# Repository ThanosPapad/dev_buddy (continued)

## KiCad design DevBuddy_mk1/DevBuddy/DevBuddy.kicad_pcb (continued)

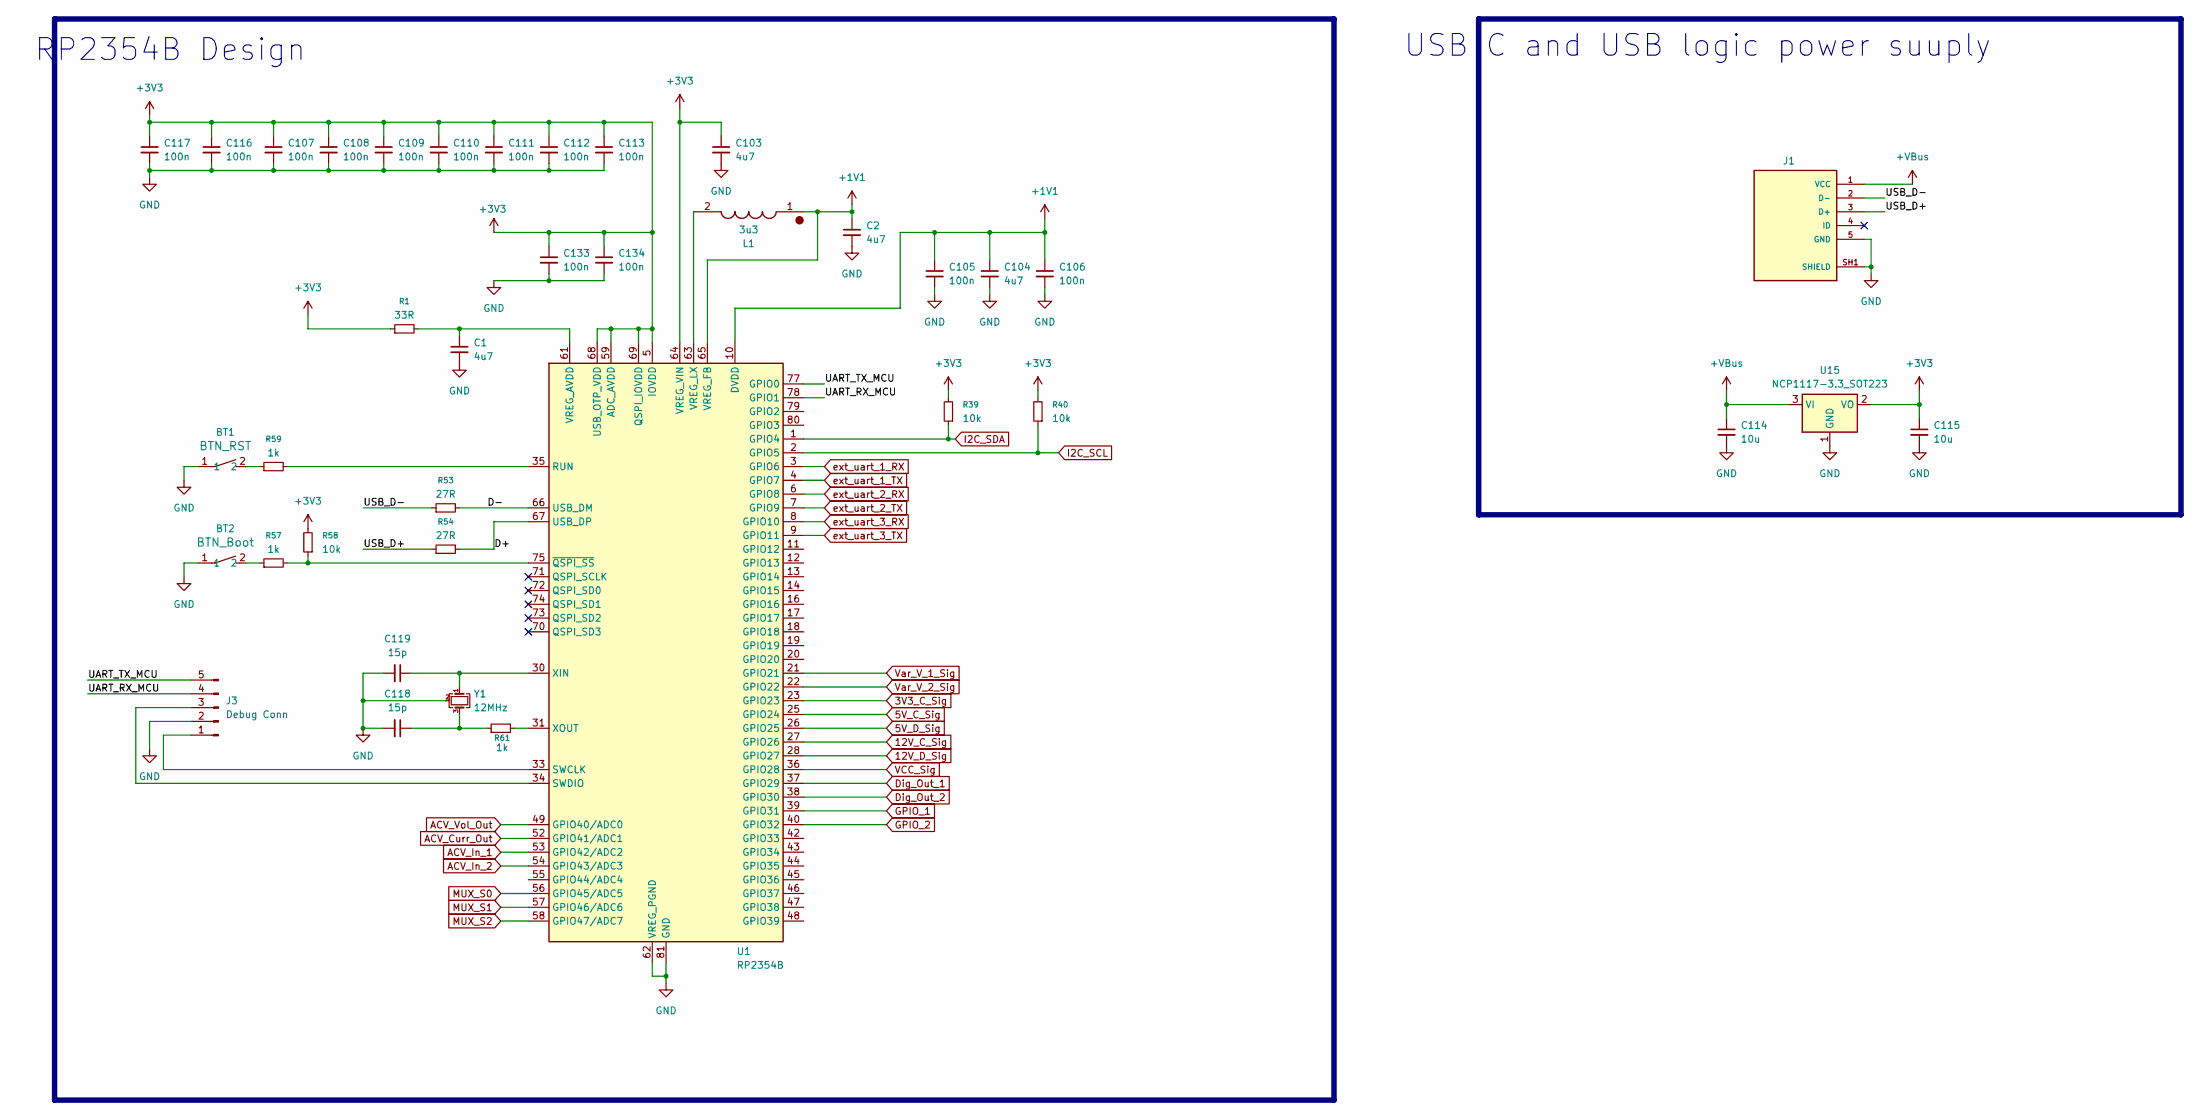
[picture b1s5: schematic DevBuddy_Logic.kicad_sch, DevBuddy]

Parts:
BT1: BTN_RST; B3U-1000P
BT2: BTN_Boot; B3U-1000P
C1, C2, C103, C104: 4u7; C_0402_1005Metric
C105, C106, C107, C108, C109, C110, C111, C112, C113, C116, C117, C133, C134: 100n; C_0402_1005Metric
C114, C115: 10u; C_0805_2012Metric
C118, C119: 15p; C_0402_1005Metric
J1: 10118194-0001LF; AMPHENOL_10118194-0001LF; PARTREV D
J3: Debug Conn; PinHeader_1x05_P2.54mm_Vertical_SMD_Pin1Left
L1: 3u3; AOTAB201610S3R3101T; Mouser Part Number 815-AB201610S3R3101T
R1: 33R; R_0402_1005Metric
R39, R40, R58: 10k; R_0402_1005Metric
R53, R54: 27R; R_0402_1005Metric
R57, R59, R61: 1k; R_0402_1005Metric
U1: RP2354B; QFN-80-1EP_10x10mm_P0.4mm_EP3.4x3.4mm
U15: NCP1117-3.3_SOT223; SOT-223-3_TabPin2
Y1: 12MHz; Crystal_SMD_3225-4Pin_3.2x2.5mm

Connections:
3V3_C_Sig: U1.23 (GPIO23); also elsewhere on the board
5V_C_Sig: U1.25 (GPIO24); also elsewhere on the board
5V_D_Sig: U1.26 (GPIO25); also elsewhere on the board
12V_C_Sig: U1.27 (GPIO26); also elsewhere on the board
12V_D_Sig: U1.28 (GPIO27); also elsewhere on the board
+1V1: C2.1, C104.1, C105.1, C106.1, L1.1, U1.10 (DVDD), U1.32 (DVDD), U1.51 (DVDD), U1.65 (VREG_FB)
+3V3: C103.1, C107.1, C108.1, C109.1, C110.1, C111.1, C112.1, C113.1, C115.1, C116.1, C117.1, C133.1, C134.1, R1.1, R39.2, R40.2, R58.2, U1.5 (IOVDD), U1.15 (IOVDD), U1.24 (IOVDD), U1.29 (IOVDD), U1.41 (IOVDD), U1.50 (IOVDD), U1.59 (ADC_AVDD), U1.60 (IOVDD), U1.64 (VREG_VIN), U1.68 (USB_OTP_VDD), U1.69 (QSPI_IOVDD), U1.76 (IOVDD), U15.2 (VO); also elsewhere on the board
+VBus: C114.1, J1.1 (VCC), U15.3 (VI)
/DevBuddy_Logic/D+: R54.2, U1.67 (USB_DP)
/DevBuddy_Logic/D-: R53.2, U1.66 (USB_DM)
/DevBuddy_Logic/UART_RX_MCU: J3.4, U1.78 (GPIO1)
/DevBuddy_Logic/UART_TX_MCU: J3.5, U1.77 (GPIO0)
/DevBuddy_Logic/USB_D+: J1.3 (D+), R54.1
/DevBuddy_Logic/USB_D-: J1.2 (D-), R53.1
ACV_Curr_Out: U1.52 (GPIO41/ADC1); also elsewhere on the board
ACV_In_1: U1.53 (GPIO42/ADC2); also elsewhere on the board
ACV_In_2: U1.54 (GPIO43/ADC3); also elsewhere on the board
ACV_Vol_Out: U1.49 (GPIO40/ADC0); also elsewhere on the board
Dig_Out_1: U1.37 (GPIO29); also elsewhere on the board
Dig_Out_2: U1.38 (GPIO30); also elsewhere on the board
GND: BT1.1, BT2.1, C1.2, C2.2, C103.2, C104.2, C105.2, C106.2, C107.2, C108.2, C109.2, C110.2, C111.2, C112.2, C113.2, C114.2, C115.2, C116.2, C117.2, C118.2, C119.2, C133.2, C134.2, J1.5 (GND), J1.SH1 (SHIELD), J1.SH2 (SHIELD), J1.SH3 (SHIELD), J1.SH4 (SHIELD), J1.SH5 (SHIELD), J1.SH6 (SHIELD), J3.2, U1.62 (VREG_PGND), U1.81 (GND), U15.1 (GND), Y1.2 (G), Y1.4 (G); also elsewhere on the board
GPIO_1: U1.39 (GPIO31); also elsewhere on the board
GPIO_2: U1.40 (GPIO32); also elsewhere on the board
I2C_SCL: R40.1, U1.2 (GPIO5); also elsewhere on the board
I2C_SDA: R39.1, U1.1 (GPIO4); also elsewhere on the board
MUX_S0: U1.56 (GPIO45/ADC5); also elsewhere on the board
MUX_S1: U1.57 (GPIO46/ADC6); also elsewhere on the board
MUX_S2: U1.58 (GPIO47/ADC7); also elsewhere on the board
unnamed: BT1.2, R59.1
unnamed: BT2.2, R57.1
unnamed: C118.1, R61.1, Y1.3
unnamed: J3.1, U1.33 (SWCLK)
unnamed: J3.3, U1.34 (SWDIO)
unnamed: R59.2, U1.35 (RUN)
unnamed: C1.1, R1.2, U1.61 (VREG_AVDD)
unnamed: L1.2, U1.63 (VREG_LX)
unnamed: C119.1, U1.30 (XIN), Y1.1
unnamed: R61.2, U1.31 (XOUT)
unnamed: R57.2, R58.1, U1.75 (~QSPI_SS)
VCC_Sig: U1.36 (GPIO28); also elsewhere on the board
Var_V_1_Sig: U1.21 (GPIO21); also elsewhere on the board
Var_V_2_Sig: U1.22 (GPIO22); also elsewhere on the board
ext_uart_1_RX: U1.3 (GPIO6); also elsewhere on the board
ext_uart_1_TX: U1.4 (GPIO7); also elsewhere on the board
ext_uart_2_RX: U1.6 (GPIO8); also elsewhere on the board
ext_uart_2_TX: U1.7 (GPIO9); also elsewhere on the board
ext_uart_3_RX: U1.8 (GPIO10); also elsewhere on the board
ext_uart_3_TX: U1.9 (GPIO11); also elsewhere on the board

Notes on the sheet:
RP2354B Design
USB C and USB logic power suuply

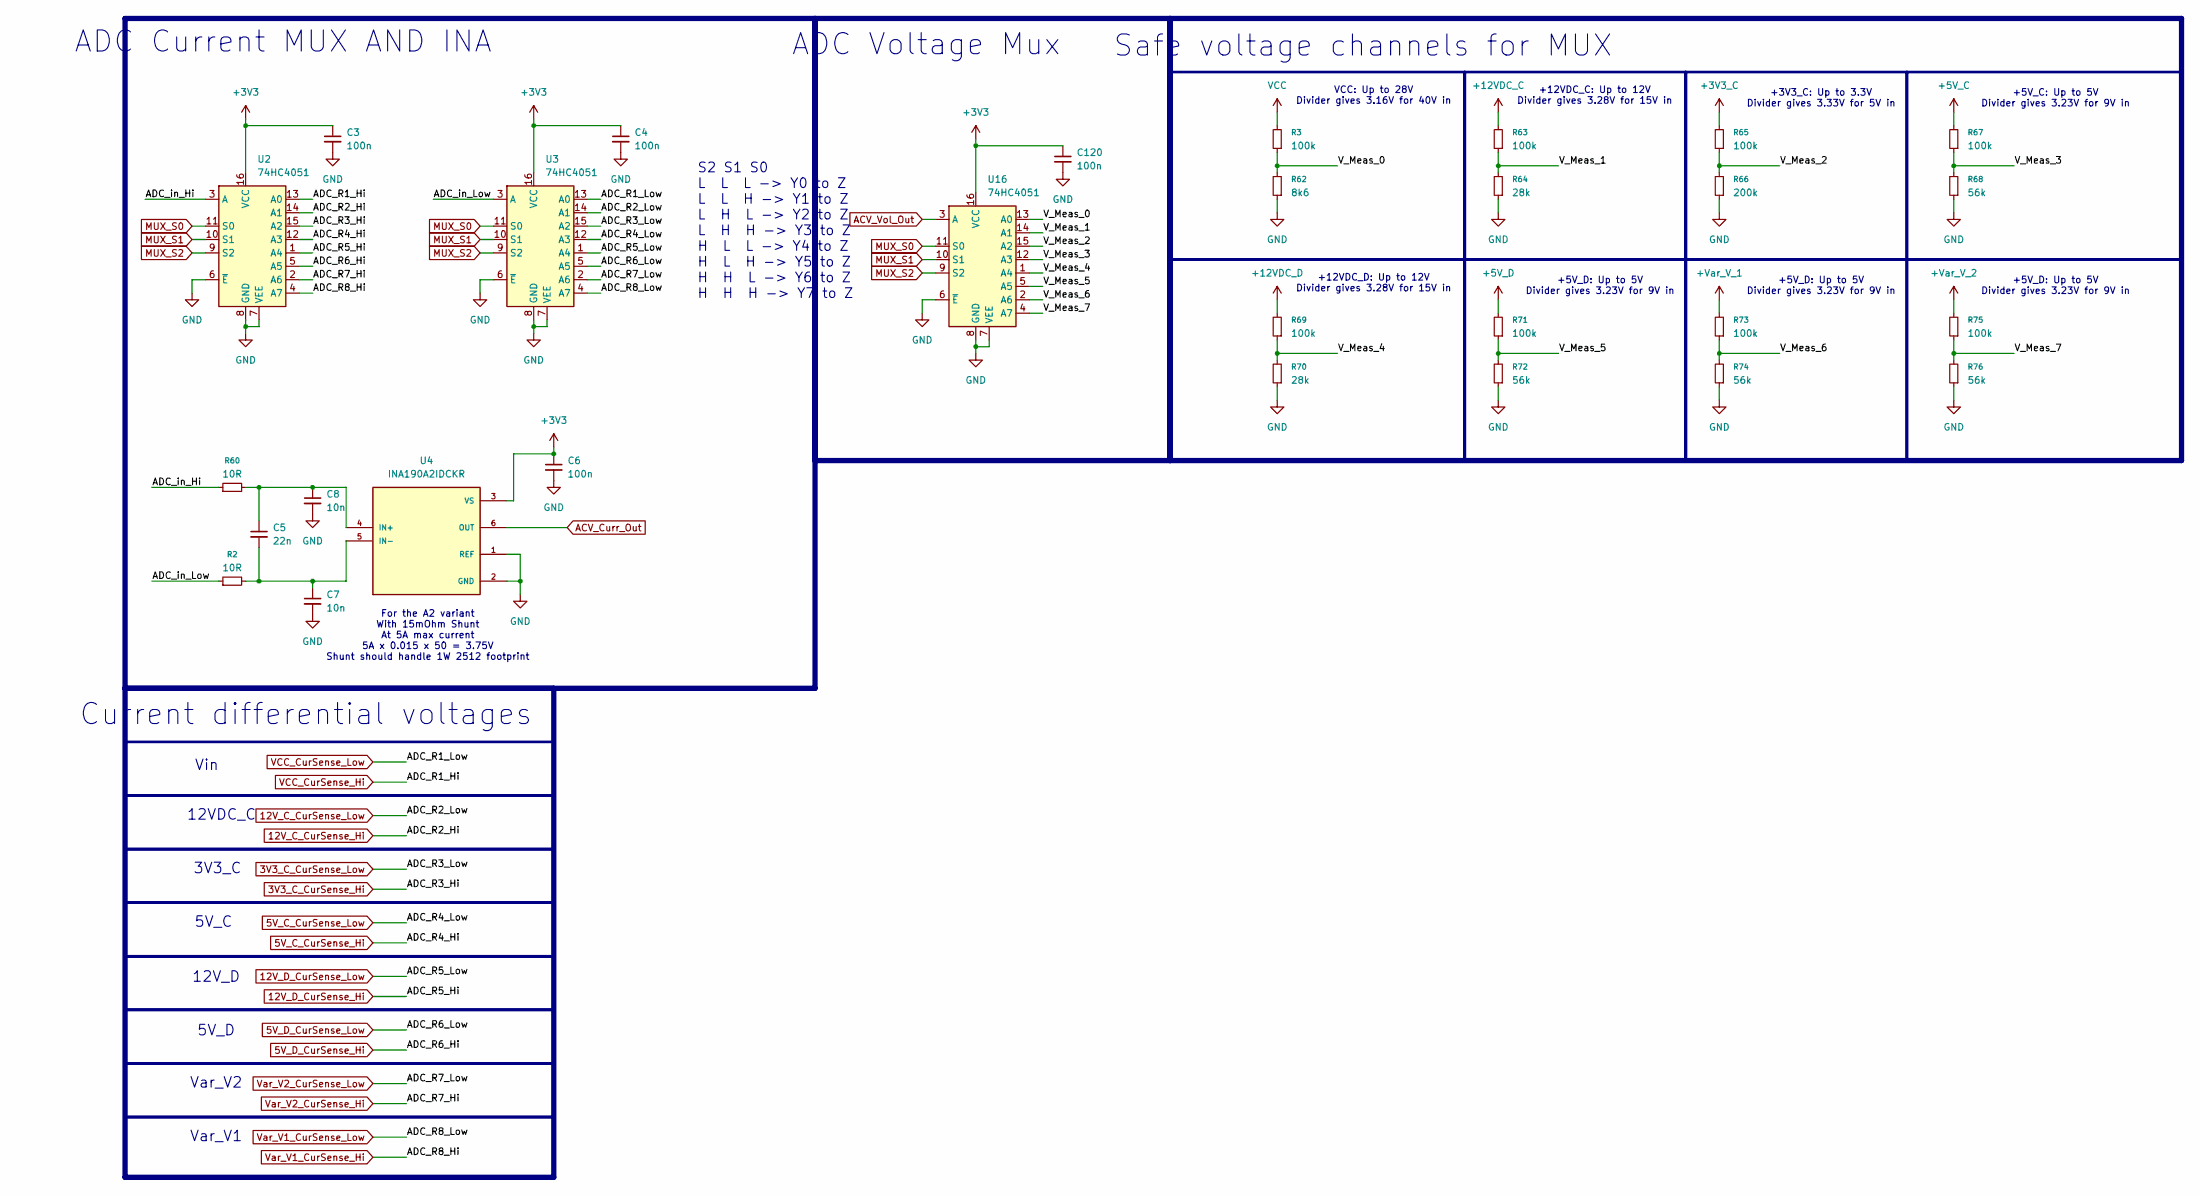
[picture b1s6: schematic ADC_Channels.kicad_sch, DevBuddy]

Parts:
C3, C4, C6, C120: 100n; C_0402_1005Metric
C5: 22n; C_0402_1005Metric
C7, C8: 10n; C_0402_1005Metric
R2, R60: 10R; R_0402_1005Metric
R3, R63, R65, R67, R69, R71, R73, R75: 100k; R_0402_1005Metric
R62: 8k6; R_0402_1005Metric
R64, R70: 28k; R_0402_1005Metric
R66: 200k; R_0402_1005Metric
R68, R72, R74, R76: 56k; R_0402_1005Metric
U2, U3, U16: 74HC4051; SOIC-16_3.9x9.9mm_P1.27mm
U4: INA190A2IDCKR; IC_INA190A2IDCKR; PARTREV D

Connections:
3V3_C_CurSense_Hi: U2.15 (A2); also elsewhere on the board
3V3_C_CurSense_Low: R65.2, U3.15 (A2); also elsewhere on the board
5V_C_CurSense_Hi: U2.12 (A3); also elsewhere on the board
5V_C_CurSense_Low: R67.2, U3.12 (A3); also elsewhere on the board
5V_D_CurSense_Hi: U2.5 (A5); also elsewhere on the board
5V_D_CurSense_Low: R71.2, U3.5 (A5); also elsewhere on the board
12V_C_CurSense_Hi: U2.14 (A1); also elsewhere on the board
12V_C_CurSense_Low: R63.2, U3.14 (A1); also elsewhere on the board
12V_D_CurSense_Hi: U2.1 (A4); also elsewhere on the board
12V_D_CurSense_Low: R69.2, U3.1 (A4); also elsewhere on the board
+3V3: C3.1, C4.1, C6.1, C120.1, U2.16 (VCC), U3.16 (VCC), U4.3 (VS), U16.16 (VCC); also elsewhere on the board
/ADC_Channels/ADC_in_Hi: R60.1, U2.3 (A)
/ADC_Channels/ADC_in_Low: R2.1, U3.3 (A)
/ADC_Channels/V_Meas_0: R3.1, R62.2, U16.13 (A0)
/ADC_Channels/V_Meas_1: R63.1, R64.2, U16.14 (A1)
/ADC_Channels/V_Meas_2: R65.1, R66.2, U16.15 (A2)
/ADC_Channels/V_Meas_3: R67.1, R68.2, U16.12 (A3)
/ADC_Channels/V_Meas_4: R69.1, R70.2, U16.1 (A4)
/ADC_Channels/V_Meas_5: R71.1, R72.2, U16.5 (A5)
/ADC_Channels/V_Meas_6: R73.1, R74.2, U16.2 (A6)
/ADC_Channels/V_Meas_7: R75.1, R76.2, U16.4 (A7)
ACV_Curr_Out: U4.6 (OUT); also elsewhere on the board
ACV_Vol_Out: U16.3 (A); also elsewhere on the board
GND: C3.2, C4.2, C6.2, C7.2, C8.2, C120.2, R62.1, R64.1, R66.1, R68.1, R70.1, R72.1, R74.1, R76.1, U2.6 (~E), U2.7 (VEE), U2.8 (GND), U3.6 (~E), U3.7 (VEE), U3.8 (GND), U4.1 (REF), U4.2 (GND), U16.6 (~E), U16.7 (VEE), U16.8 (GND); also elsewhere on the board
MUX_S0: U2.11 (S0), U3.11 (S0), U16.11 (S0); also elsewhere on the board
MUX_S1: U2.10 (S1), U3.10 (S1), U16.10 (S1); also elsewhere on the board
MUX_S2: U2.9 (S2), U3.9 (S2), U16.9 (S2); also elsewhere on the board
unnamed: C5.1, C8.1, R60.2, U4.4 (IN+)
unnamed: C5.2, C7.1, R2.2, U4.5 (IN-)
VCC_CurSense_Hi: U2.13 (A0); also elsewhere on the board
VCC_CurSense_Low: R3.2, U3.13 (A0); also elsewhere on the board
Var_V1_CurSense_Hi: U2.4 (A7); also elsewhere on the board
Var_V1_CurSense_Low: R73.2, U3.4 (A7); also elsewhere on the board
Var_V2_CurSense_Hi: U2.2 (A6); also elsewhere on the board
Var_V2_CurSense_Low: R75.2, U3.2 (A6); also elsewhere on the board

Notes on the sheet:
For the A2 variant With 15mOhm Shunt At 5A max current 5A x 0.015 x 50 = 3.75V Shunt should handle 1W 2512 footprint
12VDC_C
+5V_D: Up to 5V Divider gives 3.23V for 9V in
12V_D
Current differential voltages
+5V_C: Up to 5V Divider gives 3.23V for 9V in
S2 S1 S0 L L L -> Y0 to Z L L H -> Y1 to Z L H L -> Y2 to Z L H H -> Y3 to Z H L L -> Y4 to Z H L H -> Y5 to Z H H L -> Y6 to Z H H H -> Y7 to Z
ADC Voltage Mux
Var_V2
+12VDC_D: Up to 12V Divider gives 3.28V for 15V in
+12VDC_C: Up to 12V Divider gives 3.28V for 15V in
Safe voltage channels for MUX
3V3_C
VCC: Up to 28V Divider gives 3.16V for 40V in
+3V3_C: Up to 3.3V Divider gives 3.33V for 5V in
Vin
5V_C
5V_D
ADC Current MUX AND INA
Var_V1

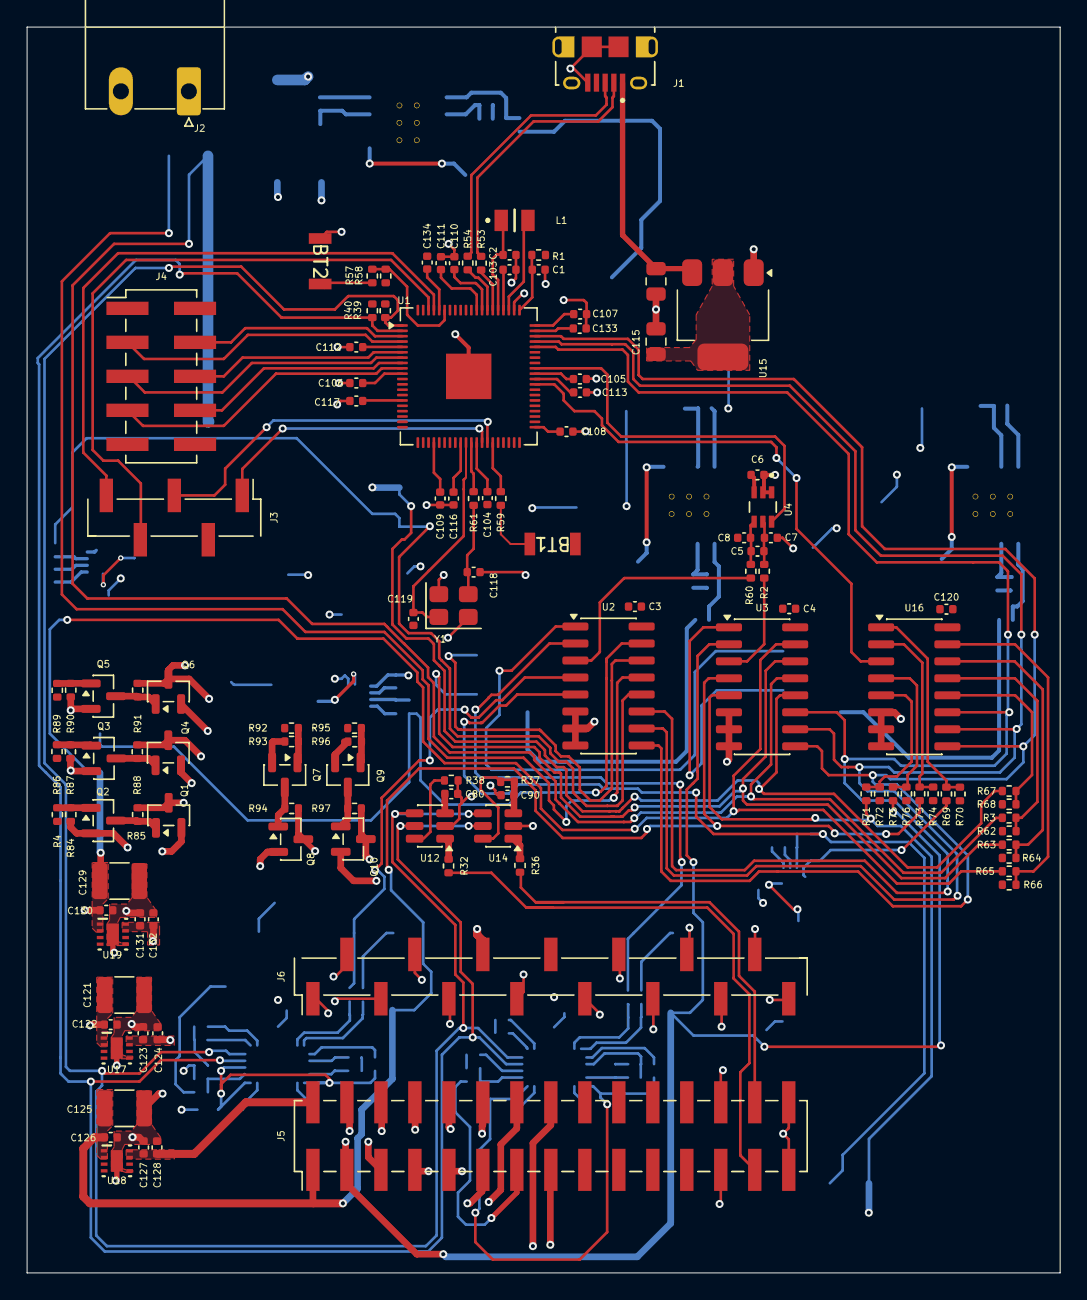
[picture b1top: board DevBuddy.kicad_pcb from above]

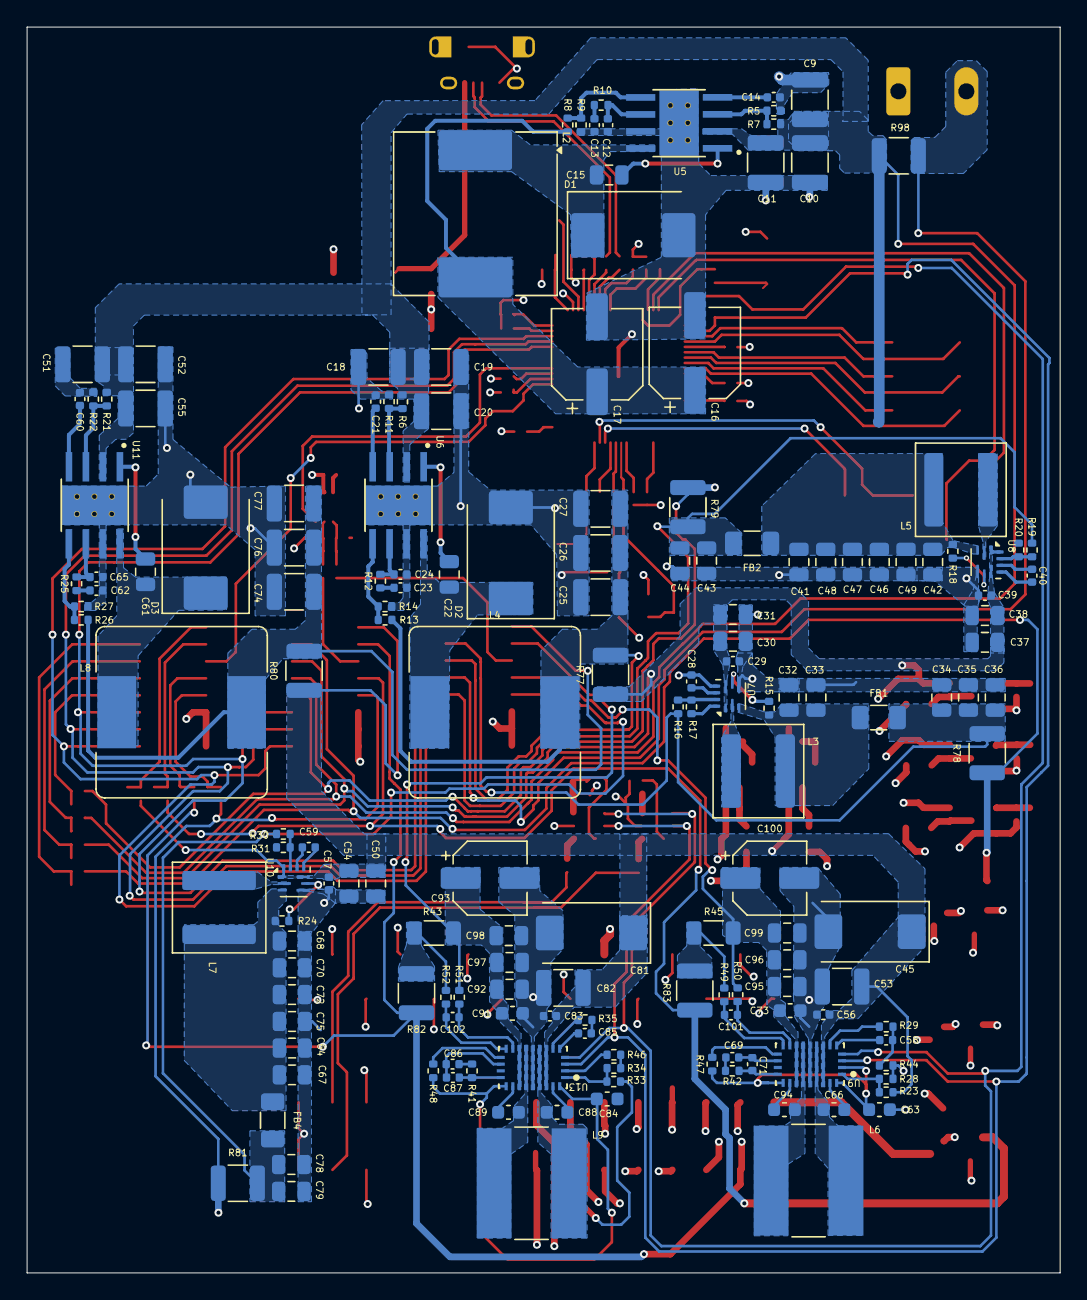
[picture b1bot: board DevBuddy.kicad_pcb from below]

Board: 4 copper layers, 77.2 x 93.1 mm, 283 parts (164 on the bottom side), 165 nets.

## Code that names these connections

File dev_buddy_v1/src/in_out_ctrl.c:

#include "in_out_ctrl.h"
#include "hardware/adc.h"
#include "uart_coms.h"
#include "i2c_drive.h"
void toggle_led()
{
    static bool led_status = 0;
    if (led_status == true){
        pico_set_led(false);
        led_status = false;
    }
    else if (led_status == false){
        pico_set_led(true);
        led_status = true;
    }
}

void pico_led_init(void)
{
    gpio_init(PICO_DEFAULT_LED_PIN);
    gpio_set_dir(PICO_DEFAULT_LED_PIN, GPIO_OUT);
}

// Turn the LED on or off
void pico_set_led(bool led_on)
{
    // Just set the GPIO on or off
    gpio_put(PICO_DEFAULT_LED_PIN, led_on);
}

void update_outputs()
{
    gpio_put((uint)CHANNEL_OUT_0, out_status.channel_0_out);
    gpio_put((uint)CHANNEL_OUT_1, out_status.channel_1_out);
    gpio_put((uint)CHANNEL_OUT_2, out_status.channel_2_out);
#ifdef OUTPUTS_READY
    gpio_put((uint)CHANNEL_OUT_0, out_status.channel_0_out);
    gpio_put((uint)CHANNEL_OUT_1, out_status.channel_1_out);
    gpio_put((uint)CHANNEL_OUT_2, out_status.channel_2_out);
    gpio_put((uint)CHANNEL_OUT_3, out_status.channel_3_out);
    gpio_put((uint)CHANNEL_OUT_4, out_status.channel_4_out);
    gpio_put((uint)CHANNEL_OUT_5, out_status.channel_5_out);
    gpio_put((uint)CHANNEL_OUT_6, out_status.channel_6_out);
    gpio_put((uint)CHANNEL_OUT_7, out_status.channel_7_out);
    gpio_put((uint)CHANNEL_OUT_8, out_status.channel_8_out);
    gpio_put((uint)CHANNEL_OUT_9, out_status.channel_9_out);
    gpio_put((uint)CHANNEL_OUT_10, out_status.channel_10_out);
#endif

    output_set_flag = false;
}

void init_outputs()
{
    gpio_init((uint)CHANNEL_OUT_0);
    gpio_set_dir((uint)CHANNEL_OUT_0, GPIO_OUT);
    gpio_init((uint)CHANNEL_OUT_1);
    gpio_set_dir((uint)CHANNEL_OUT_1, GPIO_OUT);
    gpio_init((uint)CHANNEL_OUT_2);
    gpio_set_dir((uint)CHANNEL_OUT_2, GPIO_OUT);
#ifdef OUTPUTS_READY   
    gpio_init((uint)CHANNEL_OUT_0);
    gpio_set_dir((uint)CHANNEL_OUT_0, GPIO_OUT);
    gpio_init((uint)CHANNEL_OUT_1);
    gpio_set_dir((uint)CHANNEL_OUT_1, GPIO_OUT);
    gpio_init((uint)CHANNEL_OUT_2);
    gpio_set_dir((uint)CHANNEL_OUT_2, GPIO_OUT);
    gpio_init((uint)CHANNEL_OUT_3);
    gpio_set_dir((uint)CHANNEL_OUT_3, GPIO_OUT);
    gpio_init((uint)CHANNEL_OUT_4);
    gpio_set_dir((uint)CHANNEL_OUT_4, GPIO_OUT);
    gpio_init((uint)CHANNEL_OUT_5);
    gpio_set_dir((uint)CHANNEL_OUT_5, GPIO_OUT);
    gpio_init((uint)CHANNEL_OUT_6);
    gpio_set_dir((uint)CHANNEL_OUT_6, GPIO_OUT);
    gpio_init((uint)CHANNEL_OUT_7);
    gpio_set_dir((uint)CHANNEL_OUT_7, GPIO_OUT);
    gpio_init((uint)CHANNEL_OUT_8);
    gpio_set_dir((uint)CHANNEL_OUT_8, GPIO_OUT);
    gpio_init((uint)CHANNEL_OUT_9);
    gpio_set_dir((uint)CHANNEL_OUT_9, GPIO_OUT);
    gpio_init((uint)CHANNEL_OUT_10);
    gpio_set_dir((uint)CHANNEL_OUT_10, GPIO_OUT);
#endif
    gpio_init((uint)MUX_S0_PIN);
    gpio_set_dir((uint)MUX_S0_PIN, GPIO_OUT);
    gpio_init((uint)MUX_S1_PIN);
    gpio_set_dir((uint)MUX_S1_PIN, GPIO_OUT);
    gpio_init((uint)MUX_S2_PIN);
    gpio_set_dir((uint)MUX_S2_PIN, GPIO_OUT);
}
void init_inputs()
{
#ifdef OUTPUTS_READY   
    gpio_init((uint)CHANNEL_READ_0);
    gpio_set_dir((uint)CHANNEL_READ_0, GPIO_IN);
    gpio_pull_down((uint)CHANNEL_READ_0);
    gpio_init((uint)CHANNEL_READ_1);
    gpio_set_dir((uint)CHANNEL_READ_1, GPIO_IN);
    gpio_pull_down((uint)CHANNEL_READ_1);
    gpio_init((uint)CHANNEL_READ_2);
    gpio_set_dir((uint)CHANNEL_READ_2, GPIO_IN);
    gpio_pull_down((uint)CHANNEL_READ_2);
    gpio_init((uint)CHANNEL_READ_3);
    gpio_set_dir((uint)CHANNEL_READ_3, GPIO_IN);
    gpio_pull_down((uint)CHANNEL_READ_3);
    gpio_init((uint)CHANNEL_READ_4);
    gpio_set_dir((uint)CHANNEL_READ_4, GPIO_IN);
    gpio_pull_down((uint)CHANNEL_READ_4);
    gpio_init((uint)CHANNEL_READ_5);
    gpio_set_dir((uint)CHANNEL_READ_5, GPIO_IN);
    gpio_pull_down((uint)CHANNEL_READ_5);
    gpio_init((uint)CHANNEL_READ_6);
    gpio_set_dir((uint)CHANNEL_READ_6, GPIO_IN);
    gpio_pull_down((uint)CHANNEL_READ_6);
    gpio_init((uint)CHANNEL_READ_7);
    gpio_set_dir((uint)CHANNEL_READ_7, GPIO_IN);
    gpio_pull_down((uint)CHANNEL_READ_7);
    gpio_init((uint)CHANNEL_READ_8);
    gpio_set_dir((uint)CHANNEL_READ_8, GPIO_IN);
    gpio_pull_down((uint)CHANNEL_READ_8);
    gpio_init((uint)CHANNEL_READ_9);
    gpio_set_dir((uint)CHANNEL_READ_9, GPIO_IN);
    gpio_pull_down((uint)CHANNEL_READ_9);
    gpio_init((uint)CHANNEL_READ_10);
    gpio_set_dir((uint)CHANNEL_READ_10, GPIO_IN);
    gpio_pull_down((uint)CHANNEL_READ_10);
#endif
}

void read_input_channels (input_read_t *packet)
{
#ifdef OUTPUTS_READY
    packet->channel_0_in = gpio_get((uint)CHANNEL_READ_0);
    packet->channel_0_in = gpio_get((uint)CHANNEL_READ_1);
    packet->channel_0_in = gpio_get((uint)CHANNEL_READ_2);
    packet->channel_0_in = gpio_get((uint)CHANNEL_READ_3);
    packet->channel_0_in = gpio_get((uint)CHANNEL_READ_4);
    packet->channel_0_in = gpio_get((uint)CHANNEL_READ_5);
    packet->channel_0_in = gpio_get((uint)CHANNEL_READ_6);
    packet->channel_0_in = gpio_get((uint)CHANNEL_READ_7);
    packet->channel_0_in = gpio_get((uint)CHANNEL_READ_8);
    packet->channel_0_in = gpio_get((uint)CHANNEL_READ_9);
    packet->channel_0_in = gpio_get((uint)CHANNEL_READ_10);
#else
    packet->channel_0_in = 1;
    packet->channel_1_in = 0;
    packet->channel_2_in = 1;
    packet->channel_3_in = 0;
    packet->channel_4_in = 1;
    packet->channel_5_in = 0;
    packet->channel_6_in = 1;
    packet->channel_7_in = 0;
    packet->channel_8_in = 1;
    packet->channel_9_in = 0;
    packet->channel_10_in = 1;
#endif
    read_ins_flag = false;
}

void adc_init_internal ()
{
    adc_init();
    adc_gpio_init(V_CHANNELS_ADC_PIN);
    adc_gpio_init(I_CHANNELS_ADC_PIN);

}

// Read all the channels
channel_voltages_t read_adc_channels ()
{
    channel_voltages_t res = {0};
    uint16_t raw = 0;
    const float conversion_factor = 3.3f / (1 << 12);  // 3.3V / 4096
    // TODO; Add more measurements for each reading to achieve better accuracy
    mux_select(MUX_CH0);
    busy_wait_us_32(20); // Wait for 20 micro secs for mux to settle
    adc_select_input(0); // ADC0 - (GPIO26)
    raw = adc_read();    // (0-4095)
    res.ch_adc_meas_0.voltage_meas = raw * conversion_factor;
    adc_select_input(1);
    raw = adc_read();
    res.ch_adc_meas_0.current_meas = raw * conversion_factor;

    mux_select(MUX_CH1);
    busy_wait_us_32(20);
    adc_select_input(0); // ADC0 - (GPIO26)
    raw = adc_read();    // (0-4095)
    res.ch_adc_meas_1.voltage_meas = raw * conversion_factor;
    adc_select_input(1);
    raw = adc_read();
    res.ch_adc_meas_1.current_meas = raw * conversion_factor;

    mux_select(MUX_CH2);
    busy_wait_us_32(20);
    adc_select_input(0); // ADC0 - (GPIO26)
    raw = adc_read();    // (0-4095)
    res.ch_adc_meas_2.voltage_meas = raw * conversion_factor;
    adc_select_input(1);
    raw = adc_read();
    res.ch_adc_meas_2.current_meas = raw * conversion_factor;

    mux_select(MUX_CH3);
    busy_wait_us_32(20);
    adc_select_input(0); // ADC0 - (GPIO26)
    raw = adc_read();    // (0-4095)
    res.ch_adc_meas_3.voltage_meas = raw * conversion_factor;
    adc_select_input(1);
    raw = adc_read();
    res.ch_adc_meas_3.current_meas = raw * conversion_factor;

    mux_select(MUX_CH4);
    busy_wait_us_32(20);
    adc_select_input(0); // ADC0 - (GPIO26)
    raw = adc_read();    // (0-4095)
    res.ch_adc_meas_4.voltage_meas = raw * conversion_factor;
    adc_select_input(1);
    raw = adc_read();
    res.ch_adc_meas_4.current_meas = raw * conversion_factor;

    mux_select(MUX_CH5);
    busy_wait_us_32(20);
    adc_select_input(0); // ADC0 - (GPIO26)
    raw = adc_read();    // (0-4095)
    res.ch_adc_meas_5.voltage_meas = raw * conversion_factor;
    adc_select_input(1);
    raw = adc_read();
    res.ch_adc_meas_5.current_meas = raw * conversion_factor;

    mux_select(MUX_CH6);
    busy_wait_us_32(20);
    adc_select_input(0); // ADC0 - (GPIO26)
    raw = adc_read();    // (0-4095)
    res.ch_adc_meas_6.voltage_meas = raw * conversion_factor;
    adc_select_input(1);
    raw = adc_read();
    res.ch_adc_meas_6.current_meas = raw * conversion_factor;

    mux_select(MUX_CH7);
    busy_wait_us_32(20);
    adc_select_input(0); // ADC0 - (GPIO26)
    raw = adc_read();    // (0-4095)
    res.ch_adc_meas_7.voltage_meas = raw * conversion_factor;
    adc_select_input(1);
    raw = adc_read();
    res.ch_adc_meas_7.current_meas = raw * conversion_factor;

    return res;
}
// Wrapper function in case it's needed for periodic run
void read_adc_channels_wrapper(void *ctx) 
{
    channel_voltages_t *dest = (channel_voltages_t*)ctx;
    *dest = read_adc_channels();
}

void mux_select(mux_channel_t ch) 
{
    gpio_put(MUX_S0_PIN, (ch >> 0) & 1);
    gpio_put(MUX_S1_PIN, (ch >> 1) & 1);
    gpio_put(MUX_S2_PIN, (ch >> 2) & 1);

}

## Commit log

2026-02-28 Initial upload
2026-03-01 Added read inputs, and major update to APP
2026-03-03 Hardware changes, ADC and start of power.
2026-03-04 Changes is hardware - Power
2026-03-05 Added ADC functionality, APP and firm, App not stable.
2026-03-06 Added mux control, fixed adc tlm control, fixed app, added power in PCB
2026-03-08 Changes in Variable buck - Hardware
2026-03-08 Updated ReadMe with current info
2026-03-16 Added support for DACs in APP and device
2026-03-19 Added variable voltage channels/ PCB
2026-03-19 Fixed the image in readme
2026-03-20 Heavy additions to schematic
2026-04-02 Began USB support
2026-04-02 Changed listing appearance of devices in app
2026-04-02 Finished USB bridge on device
2026-04-02 Added the dispatcher in app and a testing_leds sequence
2026-04-03 Added PIO uart channels support in device
2026-04-04 Finished PIO uart support RX&TX device & App
2026-04-05 Added uart comms in dispatcher
2026-04-27 More work into the PCB, mainly connectors
2026-05-16 PCB, starting the board
2026-05-18 PCB, initial routing of submods
2026-05-19 PCB, first draft of PCB layout
2026-05-21 PCB, Progress in routing.
2026-05-26 PCB, Power routing nearly complete.
